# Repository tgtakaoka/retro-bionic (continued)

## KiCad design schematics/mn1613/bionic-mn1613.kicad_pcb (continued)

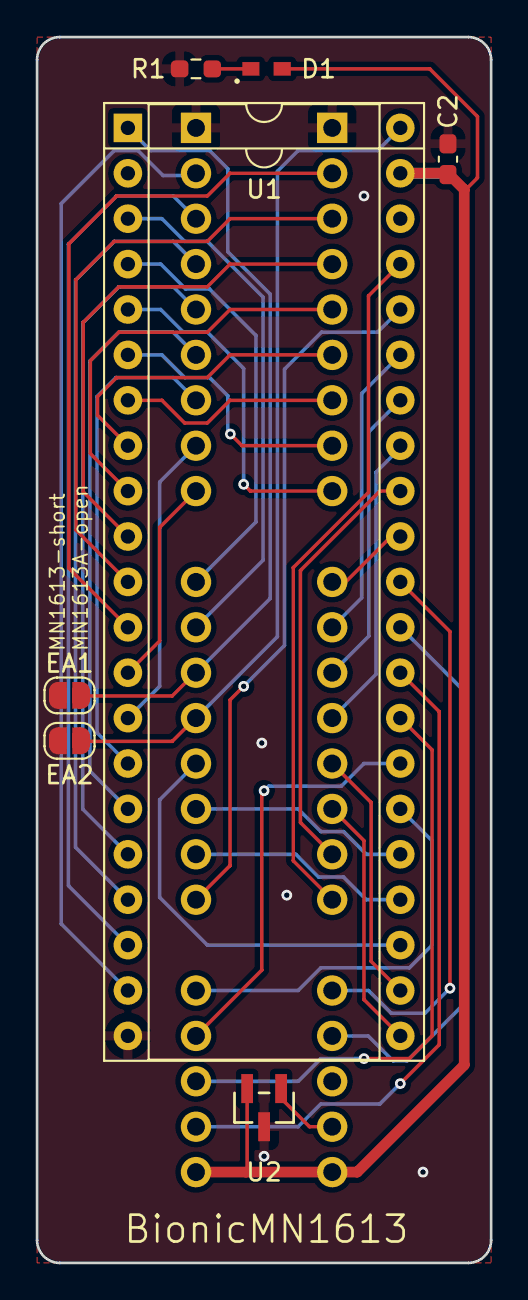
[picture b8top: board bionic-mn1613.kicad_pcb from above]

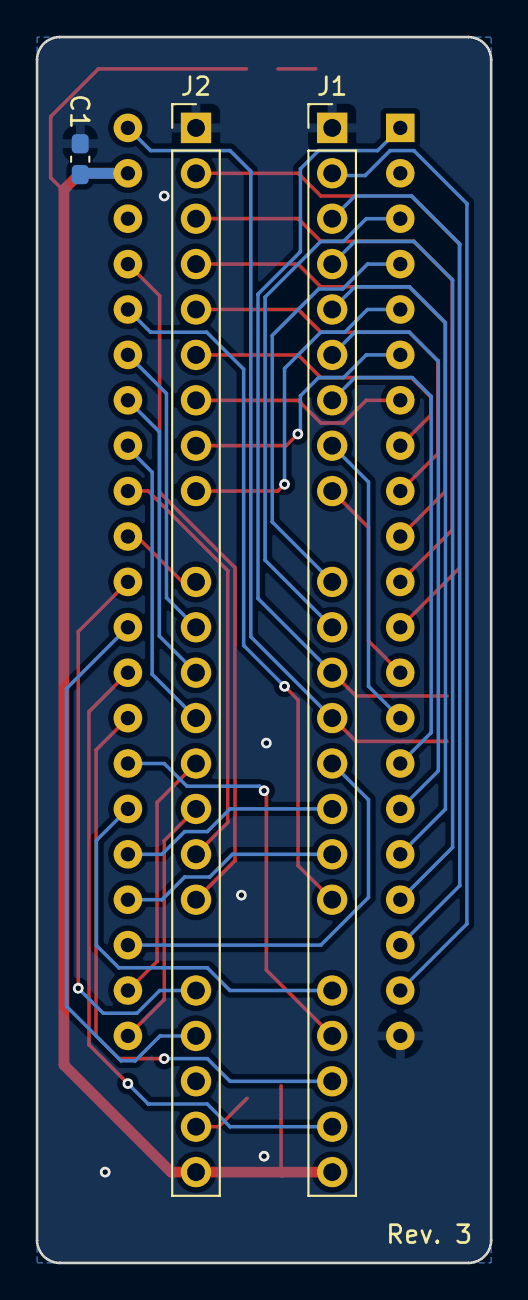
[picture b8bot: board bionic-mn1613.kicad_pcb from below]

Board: 2 copper layers, 25.4 x 68.6 mm, 10 parts (3 on the bottom side), 42 nets.
